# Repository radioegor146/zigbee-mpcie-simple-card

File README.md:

# zigbee-mpcie-simple-card

Simple but effective ZigBee mPCIe card based on CC2538 module and CP2102 USB<->UART bridge

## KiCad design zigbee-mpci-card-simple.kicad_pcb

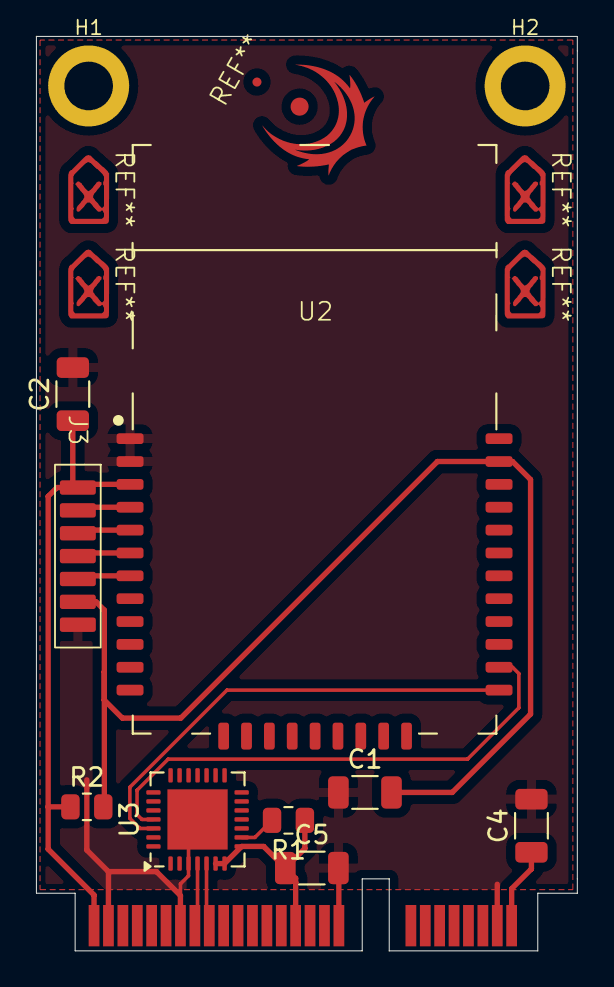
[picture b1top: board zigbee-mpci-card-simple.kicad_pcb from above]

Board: 2 copper layers, 30.0 x 50.8 mm, 12 parts (1 on the bottom side), 12 nets.

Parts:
C1: 1nF; C_1206_3216Metric
C2, C4, C5: 0.1uF; C_1206_3216Metric
H1, H2: MountingHole_Pad; MountingHole_2.7mm_M2.5_ISO7380_Pad
J1: Bus_PCI_Express_Mini; Mini_PCIe_Side1
J3: JTAG; JTAG_TestPoints
R1, R2: 4k7; R_0805_2012Metric
U2: CC2538; CC2538_Module
U3: CP2102N-Axx-xQFN28; QFN-28-1EP_5x5mm_P0.5mm_EP3.35x3.35mm

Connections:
+3.3V: C2.1, C4.1, C5.1, J1.2 (+3V3AUX), J1.24 (+3V3AUX), J1.52 (+3V3AUX), J3.1, R1.1, R2.1, U2.3 (VCC), U3.6 (VDD), U3.7 (VREGIN), U3.8 (VBUS)
GND: C1.1, C2.2, C4.2, C5.2, J1.4 (GND), J1.18 (GND), J1.26 (GND), J1.34 (GND), J1.40 (GND), J1.50 (GND), J3.7, U2.1 (GND), U2.2 (GND), U3.3 (GND), U3.29 (GND)
unnamed: R1.2, U3.9 (~RST)
RXD: U2.23 (PA1), U3.25 (RXD)
TCK: J3.3, U2.5 (TCK)
TDI: J3.5, U2.7 (PB6/TDI)
TDO: J3.4, U2.6 (PB7/TDO)
TMS: J3.2, U2.4 (TMS)
TXD: U2.22 (PA0), U3.26 (TXD)
USB_D+: J1.38 (USB_D+), U3.4 (D+)
USB_D-: J1.36 (USB_D-), U3.5 (D-)
~RESET: C1.2, J3.6, R2.2, U2.32 (RST)

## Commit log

2024-10-27 main commit
2024-10-27 rename repo
